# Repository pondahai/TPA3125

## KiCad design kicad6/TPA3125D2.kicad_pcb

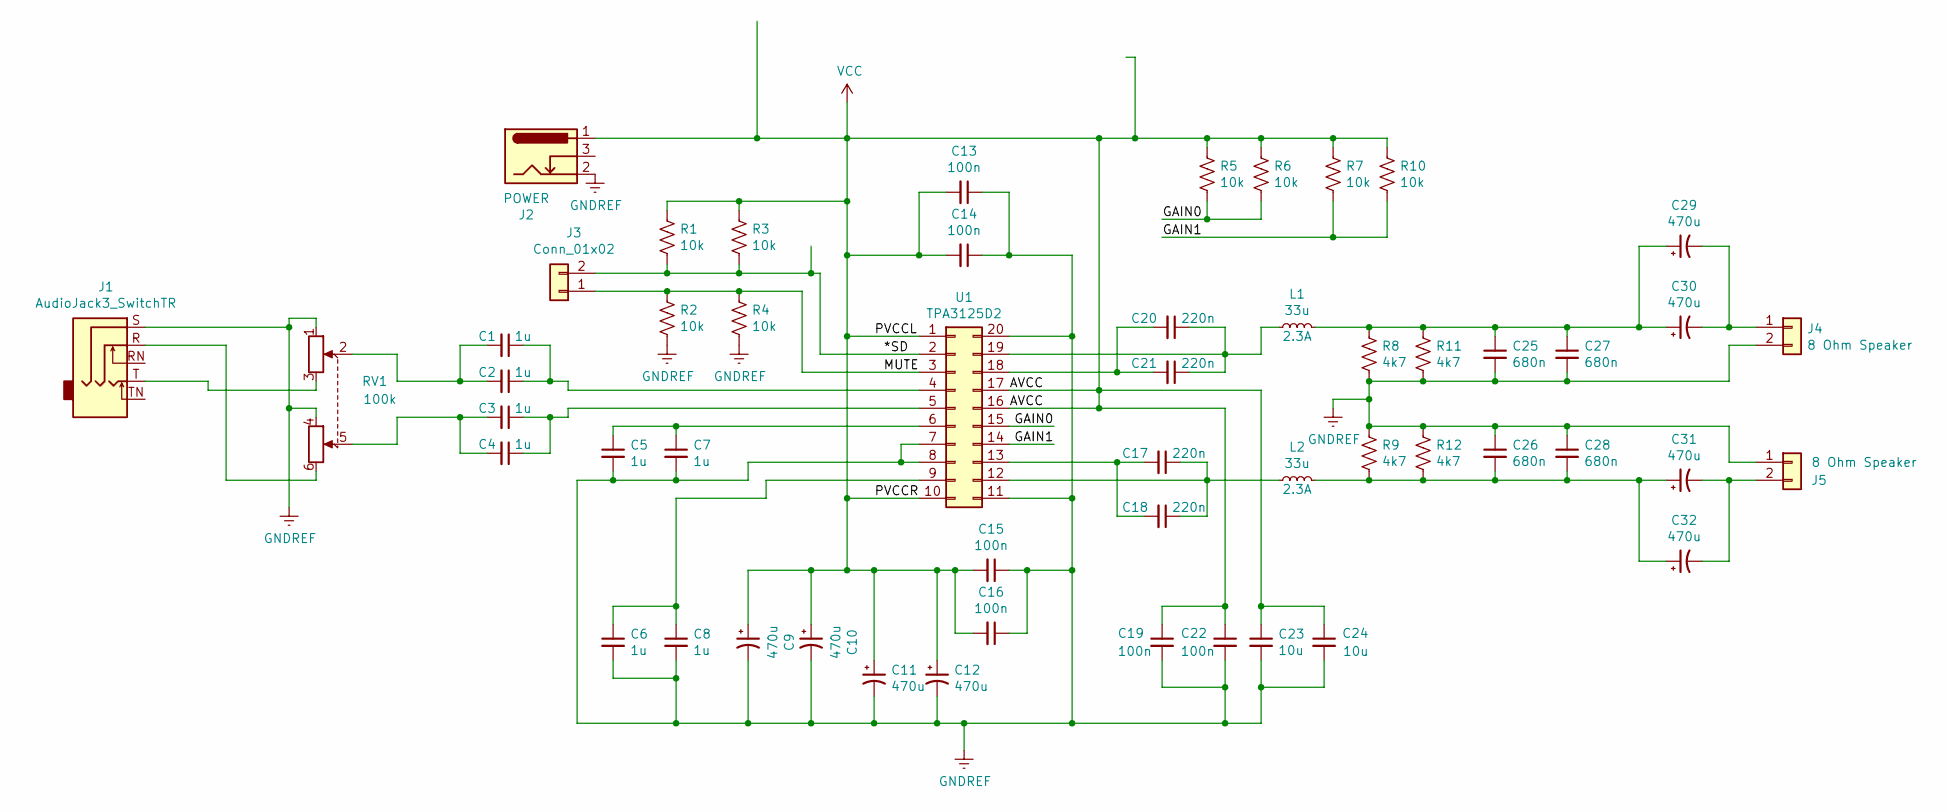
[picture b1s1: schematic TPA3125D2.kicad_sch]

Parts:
C1, C4, C5, C6: 1u; C_0603_1608Metric_Pad1.08x0.95mm_HandSolder
C2, C3, C7, C8: 1u; CP_Radial_D8.0mm_P3.50mm
C9, C10, C29, C32: 470u; CP_Radial_D10.0mm_P7.50mm
C11, C12, C30, C31: 470u; CP_Elec_10x7.7
C13, C16, C19: 100n; C_0603_1608Metric_Pad1.08x0.95mm_HandSolder
C14, C15, C22: 100n; C_Rect_L7.2mm_W2.5mm_P5.00mm_FKS2_FKP2_MKS2_MKP2
C17, C21: 220n; C_0805_2012Metric_Pad1.18x1.45mm_HandSolder
C18, C20: 220n; C_Rect_L7.2mm_W2.5mm_P5.00mm_FKS2_FKP2_MKS2_MKP2
C23: 10u; C_0805_2012Metric_Pad1.18x1.45mm_HandSolder
C24: 10u; C_Rect_L7.2mm_W2.5mm_P5.00mm_FKS2_FKP2_MKS2_MKP2
C25, C26: 680n; C_0805_2012Metric_Pad1.18x1.45mm_HandSolder
C27, C28: 680n; C_Rect_L7.2mm_W2.5mm_P5.00mm_FKS2_FKP2_MKS2_MKP2
J1: AudioJack3_SwitchTR; audiojack-3.5mm-5p
J2: POWER; BarrelJack_Horizontal
J3: Conn_01x02; Molex_SL_171971-0002_1x02_P2.54mm_Vertical
J4, J5: 8 Ohm Speaker; Molex_SL_171971-0002_1x02_P2.54mm_Vertical
L1, L2: 33u; L_Axial_L26.0mm_D9.0mm_P5.08mm_Vertical_Fastron_77A
R1, R2, R6, R10: 10k; R_Axial_DIN0411_L9.9mm_D3.6mm_P5.08mm_Vertical
R3, R4, R5, R7: 10k; R_0805_2012Metric_Pad1.20x1.40mm_HandSolder
R8, R9: 4k7; R_0805_2012Metric_Pad1.20x1.40mm_HandSolder
R11, R12: 4k7; R_Axial_DIN0411_L9.9mm_D3.6mm_P5.08mm_Vertical
RV1: 100k; Potentiometer_Alps_RK163_Dual_Horizontal
U1: TPA3125D2; DIP-20_W7.62mm_LongPads

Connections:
/*SD: J3.2, R1.2, R3.2, U1.2
/GAIN0: R5.2, R6.2, U1.15
/GAIN1: R7.2, R10.2, U1.14
/MUTE: J3.1, R2.1, R4.1, U1.3
GNDREF: C5.2, C6.2, C7.2, C8.2, C9.2, C10.2, C11.2, C12.2, C13.1, C14.1, C15.1, C16.1, C19.2, C22.2, C23.2, C24.2, C25.2, C26.1, C27.2, C28.1, J1.S, J2.2, J4.2, J5.1, R2.2, R4.2, R8.2, R9.1, R11.2, R12.1, RV1.1, RV1.4, U1.7, U1.8, U1.11, U1.20
unnamed: C1.1, C2.1, U1.4
unnamed: C1.2, C2.2, RV1.2
unnamed: C3.1, C4.1, U1.5
unnamed: C3.2, C4.2, RV1.5
unnamed: C5.1, C7.1, U1.6
unnamed: C6.1, C8.1, U1.9
unnamed: C17.1, C18.1, L2.1, U1.12
unnamed: C17.2, C18.2, U1.13
unnamed: C20.1, C21.1, L1.1, U1.19
unnamed: C20.2, C21.2, U1.18
unnamed: C25.1, C27.1, C29.1, C30.1, L1.2, R8.1, R11.1
unnamed: C26.2, C28.2, C31.1, C32.1, L2.2, R9.2, R12.2
unnamed: C29.2, C30.2, J4.1
unnamed: C31.2, C32.2, J5.2
unnamed: J1.R, RV1.6
unnamed: J1.T, RV1.3
VCC: C9.1, C10.1, C11.1, C12.1, C13.2, C14.2, C15.2, C16.2, C19.1, C22.1, C23.1, C24.1, J2.1, R1.1, R3.1, R5.1, R6.1, R7.1, R10.1, U1.1, U1.10, U1.16, U1.17

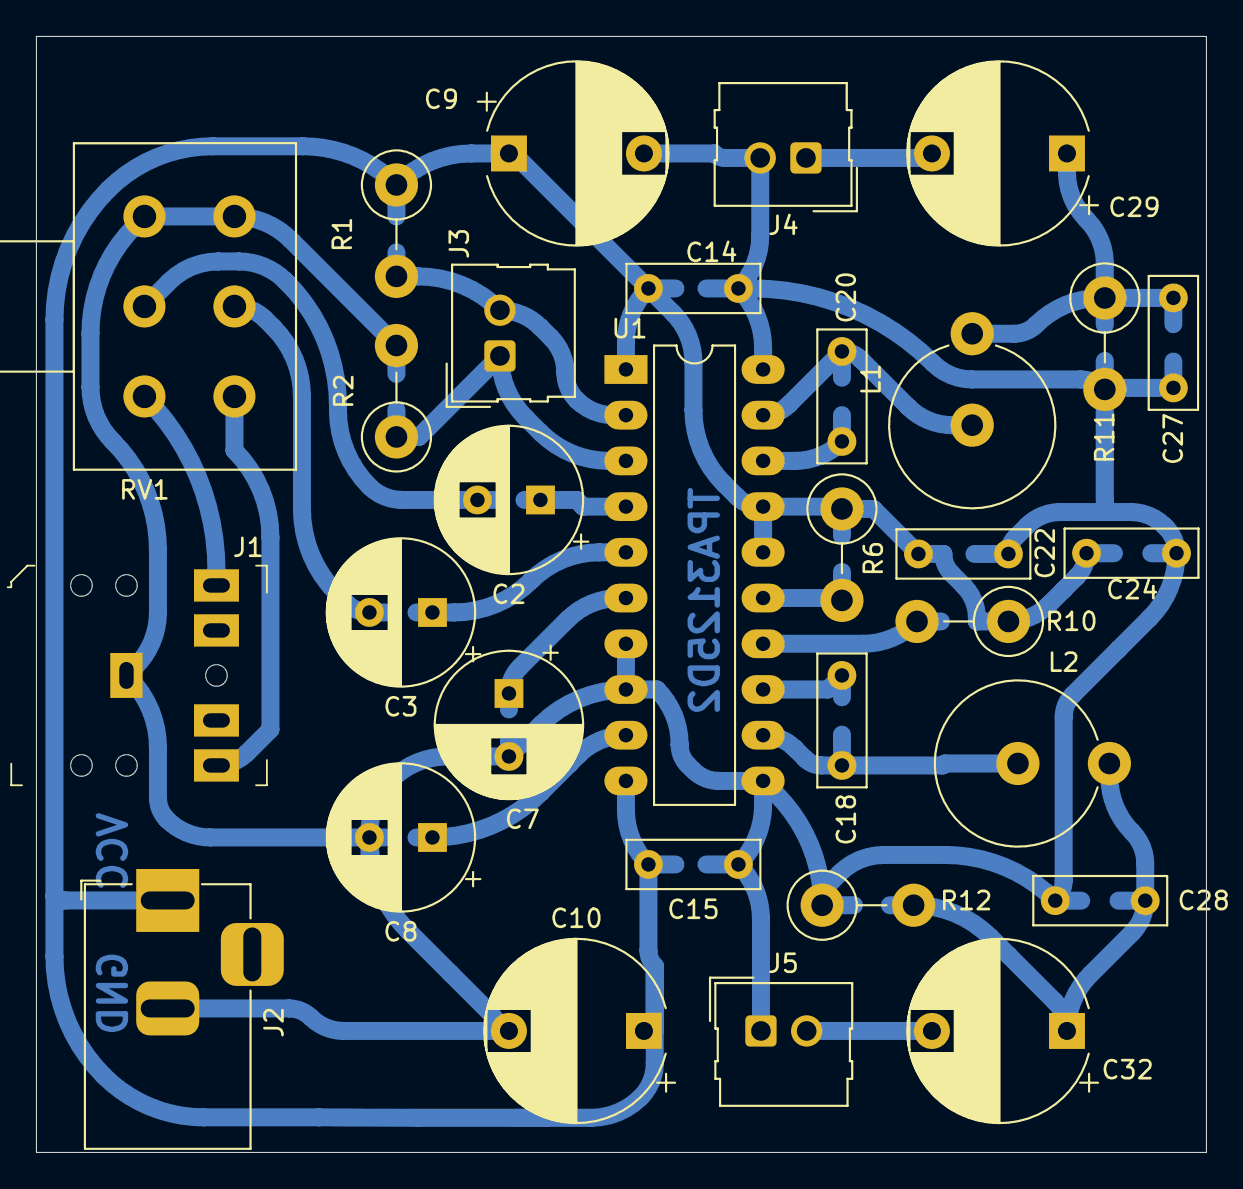
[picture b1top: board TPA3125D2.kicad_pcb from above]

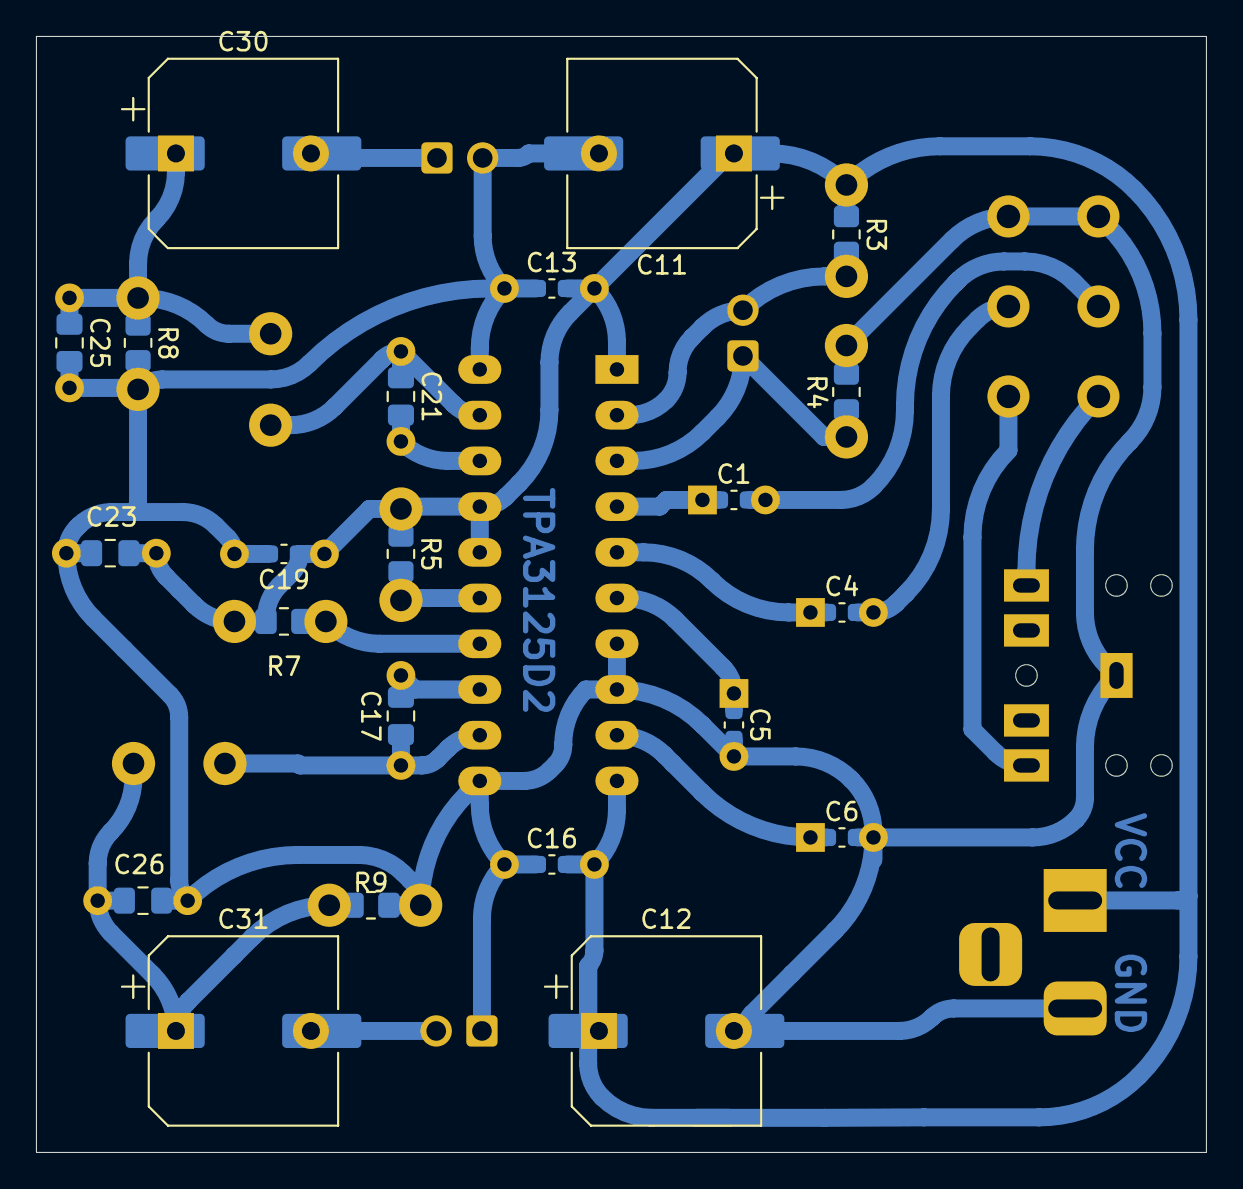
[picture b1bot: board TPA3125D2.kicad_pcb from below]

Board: 2 copper layers, 65.0 x 62.0 mm, 53 parts (22 on the bottom side), 22 nets.
